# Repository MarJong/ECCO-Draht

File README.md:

# ECCO-Draht
Archiv zum Arbeitsstand des heißen Drahtes des Elektronik Club Cottbus (ECCO). Die finalen Daten sind verloren.

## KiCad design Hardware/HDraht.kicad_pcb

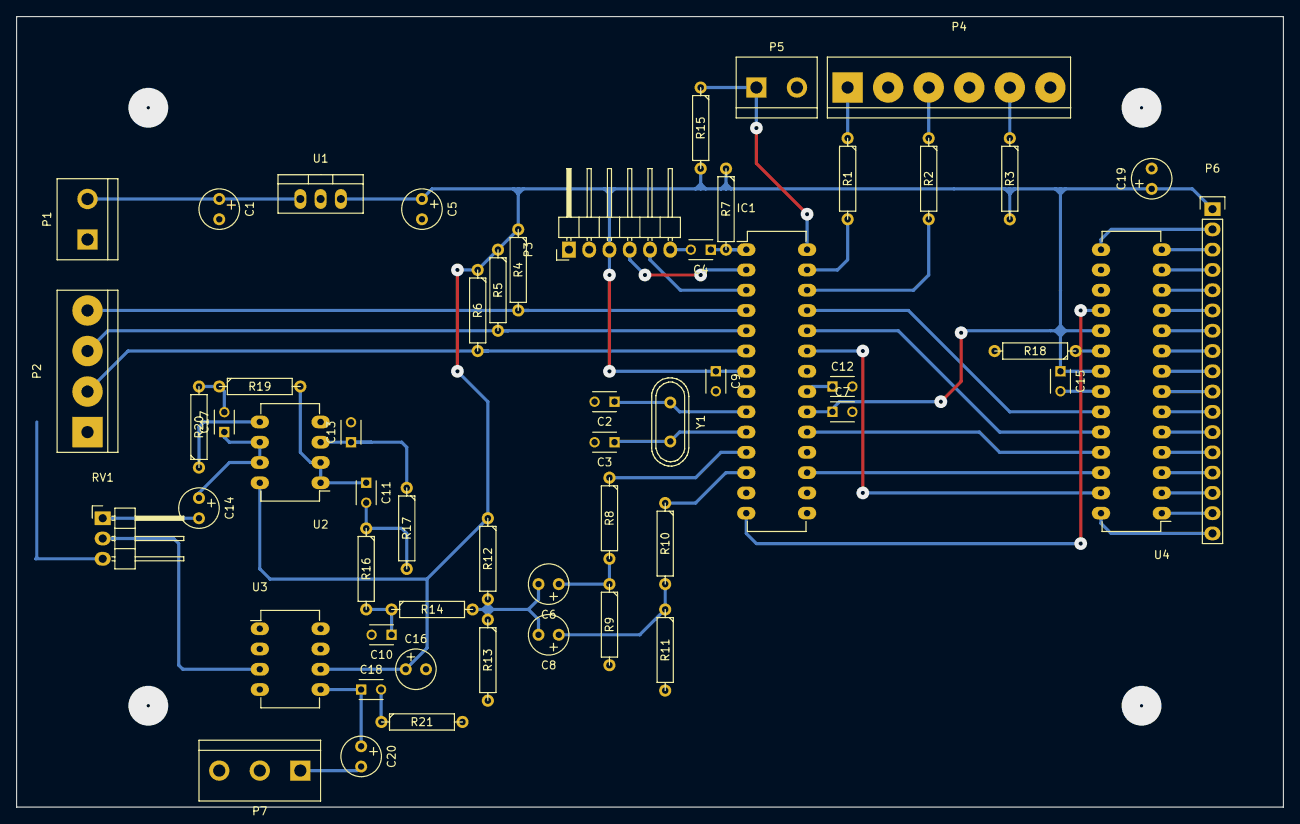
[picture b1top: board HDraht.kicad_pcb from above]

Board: 2 copper layers, 158.8 x 99.1 mm, 55 parts (0 on the bottom side), 59 nets.

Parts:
C1: 10µ; Elko_vert_11x5mm_RM2.5
C2, C3: 22p; C_Disc_D3_P2.5
C4, C7, C9, C12, C15: 100n; C_Disc_D3_P2.5
C5, C6, C8, C14, C16: 100µ; Elko_vert_11x5mm_RM2.5_CopperClear
C10: 680p; C_Disc_D3_P2.5
C11: 330p; C_Disc_D3_P2.5
C13: 47p; C_Disc_D3_P2.5
C17: 6,8n; C_Disc_D3_P2.5
C18: 50n; C_Disc_D3_P2.5
C19: 10µ; Elko_vert_11x5mm_RM2.5_CopperClear
C20: 250µ; Elko_vert_11x5mm_RM2.5_CopperClear
IC1: ATMEGA328-P; DIP-28_W7.62mm_LongPads
P1: CONN_POWER; bornier2
P2: CONN_DRAHT; bornier4
P3: CONN_USB-Seriell; Pin_Header_Angled_1x06
P4: CONN_LED; bornier6
P5: CONN_SCHALTER; bornier2
P6: CONN_01X17; Pin_Header_Straight_1x17
P7: CONN_SPEAKER; bornier3
R1, R2, R3: 200; R4
R4, R5, R6: 1k; R4
R7, R12, R13, R15: 10k; R4
R8, R10: 680k; R4
R9, R11: 33k; R4
R14: 12k; R4
R16: 110k; R4
R17: 36k; R4
R18: 2k; R4
R19: 6,2k; R4
R20: 22k; R4
R21: 10; R4
RV1: POT; Pin_Header_Angled_1x03
U1: 7805; TO-220_Neutral123_Vertical
U2: LM358N; DIP-8_W7.62mm_LongPads
U3: LM386; DIP-8_W7.62mm_LongPads
U4: TLC5940; DIP-28_W7.62mm_LongPads
Y1: 16MHz; Crystal_HC49-U_Vertical

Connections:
+5V: C5.1, C7.1, C9.1, C15.1, C16.1, C19.1, IC1.7, IC1.20, P3.3, P6.1, R3.2, R4.1, R5.1, R6.1, R7.1, R12.1, R15.2, U1.3, U2.8, U3.6, U4.19, U4.21
/BLANK: IC1.25, U4.23
/CLKO: IC1.14, U4.18
/LATCH: IC1.24, U4.24
/SCLK: IC1.19, U4.25
/SIN: IC1.17, U4.26
/VPRG: IC1.23, U4.27
/audio_1: IC1.11, R8.1
/audio_2: IC1.12, R10.1
/audio_filter_out: C14.1, C17.1, U2.6, U2.7
/draht: IC1.6, P2.2, R6.2
/ende: IC1.5, P2.3, R5.2
/led_bereit: IC1.27, R1.2
/led_fehler: IC1.26, R2.2
/start: IC1.4, P2.4, R4.2
GND: C1.2, C2.2, C3.2, C5.2, C7.2, C9.2, C10.2, C12.2, C13.2, C15.2, C16.2, C19.2, IC1.8, IC1.22, P1.1, P2.1, P3.2, P4.2, P4.4, P4.6, P5.2, P7.3, R9.2, R11.2, R13.2, R18.2, R21.2, RV1.3, U1.2, U2.4, U3.2, U3.4, U4.22
unnamed: C1.1, P1.2, U1.1
unnamed: C2.1, IC1.9, Y1.1
unnamed: C3.1, IC1.10, Y1.2
unnamed: C4.1, IC1.1, R7.2
unnamed: C4.2, P3.6
unnamed: C6.1, R8.2, R9.1
unnamed: C6.2, C8.2, R12.2, R13.1, R14.2
unnamed: C8.1, R10.2, R11.1
unnamed: C10.1, R14.1, R16.2
unnamed: C11.1, R19.2, U2.1, U2.2
unnamed: C11.2, R16.1, R17.2
unnamed: C12.1, IC1.21
unnamed: C13.1, R17.1, U2.3
unnamed: C14.2, RV1.1
unnamed: C17.2, R19.1, R20.2
unnamed: C18.1, C20.1, U3.5
unnamed: C18.2, R21.1
unnamed: C20.2, P7.1
unnamed: IC1.2, P3.4
unnamed: IC1.3, P3.5
unnamed: IC1.28, P5.1, R15.1
unnamed: P4.1, R1.1
unnamed: P4.3, R2.1
unnamed: P4.5, R3.1
unnamed: P6.2, U4.15
unnamed: P6.3, U4.14
unnamed: P6.4, U4.13
unnamed: P6.5, U4.12
unnamed: P6.6, U4.11
unnamed: P6.7, U4.10
unnamed: P6.8, U4.9
unnamed: P6.9, U4.8
unnamed: P6.10, U4.7
unnamed: P6.11, U4.6
unnamed: P6.12, U4.5
unnamed: P6.13, U4.4
unnamed: P6.14, U4.3
unnamed: P6.15, U4.2
unnamed: P6.16, U4.1
unnamed: P6.17, U4.28
unnamed: R18.1, U4.20
unnamed: R20.1, U2.5
unnamed: RV1.2, U3.3

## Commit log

2023-09-17 Archivierung
